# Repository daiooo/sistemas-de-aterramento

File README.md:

Sistemas de Aterramento
=======

Projeto: Sistemas de Aterramento

### Equipe:
* Ricardo Thé
* Tobias Fernandes
* Rodrigo Paulino
* Felipe Bandeira 
* Franscico Alexandre
* António Thé
* Henrique
* Rooney
* Kristian 
* Alberto de Castro

felipeband18 at gmail dot com

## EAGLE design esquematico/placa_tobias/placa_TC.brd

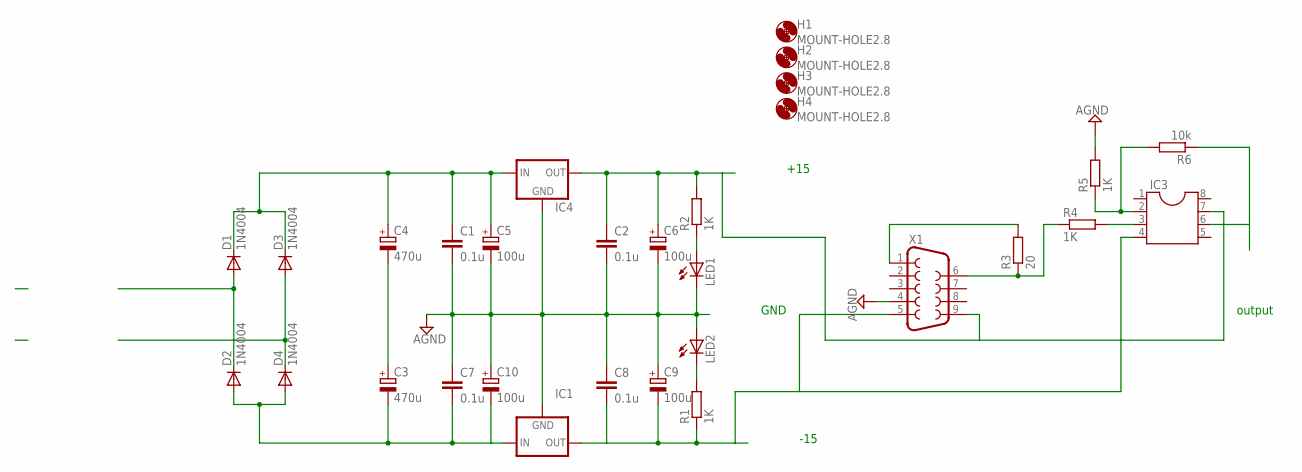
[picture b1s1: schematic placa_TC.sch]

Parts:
C1, C2, C7, C8: 0.1u; C025-024X044
C3, C4: 470u; E5-10,5
C5, C6, C9, C10: 100u; E5-10,5
D1, D2, D3, D4: 1N4004; DO41-10
H1, H2, H3, H4: MOUNT-HOLE2.8; 2,8
IC1: 79XXS
IC3: DIL8; DIL08
IC4: 78XXS
LED1, LED2: LED3MM
R1, R2, R4, R5: 1K; 0207/10
R3: 20; 0207/10
R6: 10k; 0207/10
X1: F09HP

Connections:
15V+: C1.1, C4.+, C5.+, D1.C, D3.C, IC4.IN
+15V: C2.1, C6.+, IC3.7, IC4.OUT, R2.2, X1.9
-15V: C3.-, C7.2, C10.-, D2.A, D4.A, IC1.IN
AGND: C1.2, C2.2, C5.-, C6.-, C7.1, C8.1, C9.+, C10.+, IC1.GND, IC4.GND, LED1.K (C), LED2.A, R5.2, X1.4
M15: C8.2, C9.-, IC1.OUT, IC3.4, R1.1, X1.5
unnamed: C3.+, C4.-
unnamed: D3.A, D4.C
unnamed: D1.A, D2.C
unnamed: IC3.3, R4.2
unnamed: IC3.2, R5.1, R6.2
unnamed: R3.1, R4.1, X1.6
unnamed: LED2.K (C), R1.2
unnamed: R3.2, X1.1
unnamed: LED1.A, R2.1
OUT: IC3.6, R6.1

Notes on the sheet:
output
GND
+15
-15

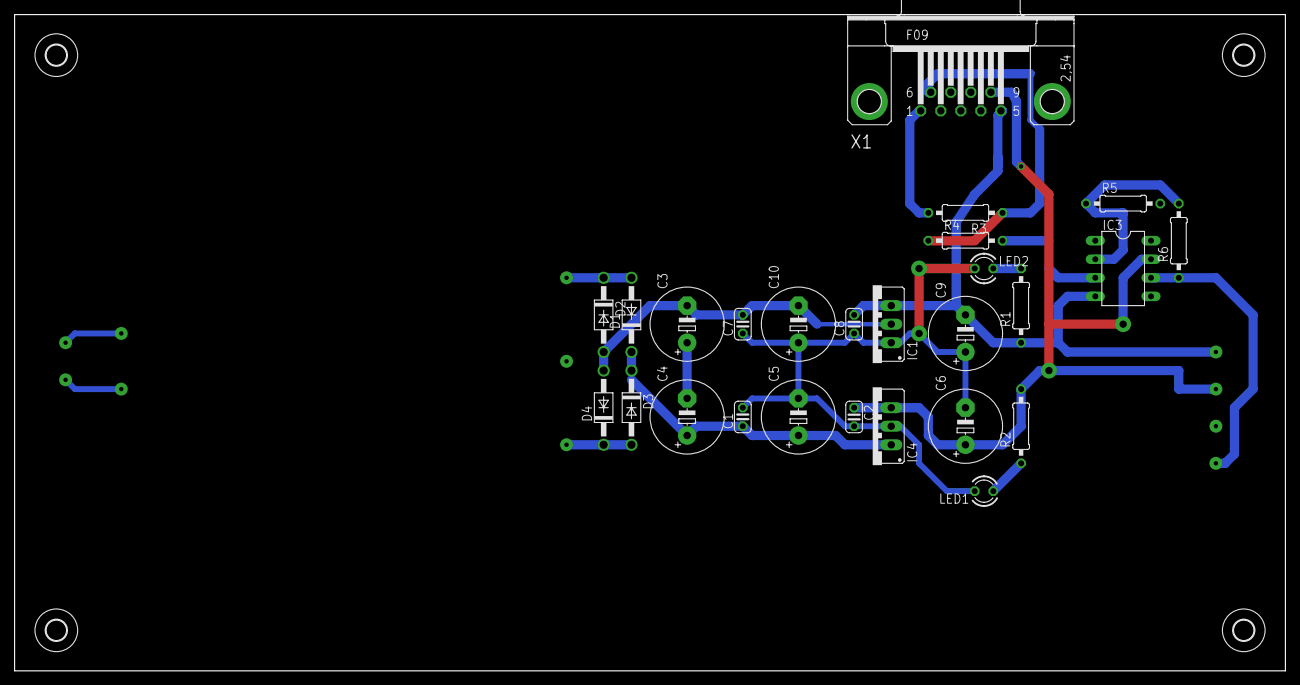
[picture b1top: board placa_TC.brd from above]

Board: 2 copper layers, 174.0 x 89.8 mm, 30 parts (0 on the bottom side), 15 nets.

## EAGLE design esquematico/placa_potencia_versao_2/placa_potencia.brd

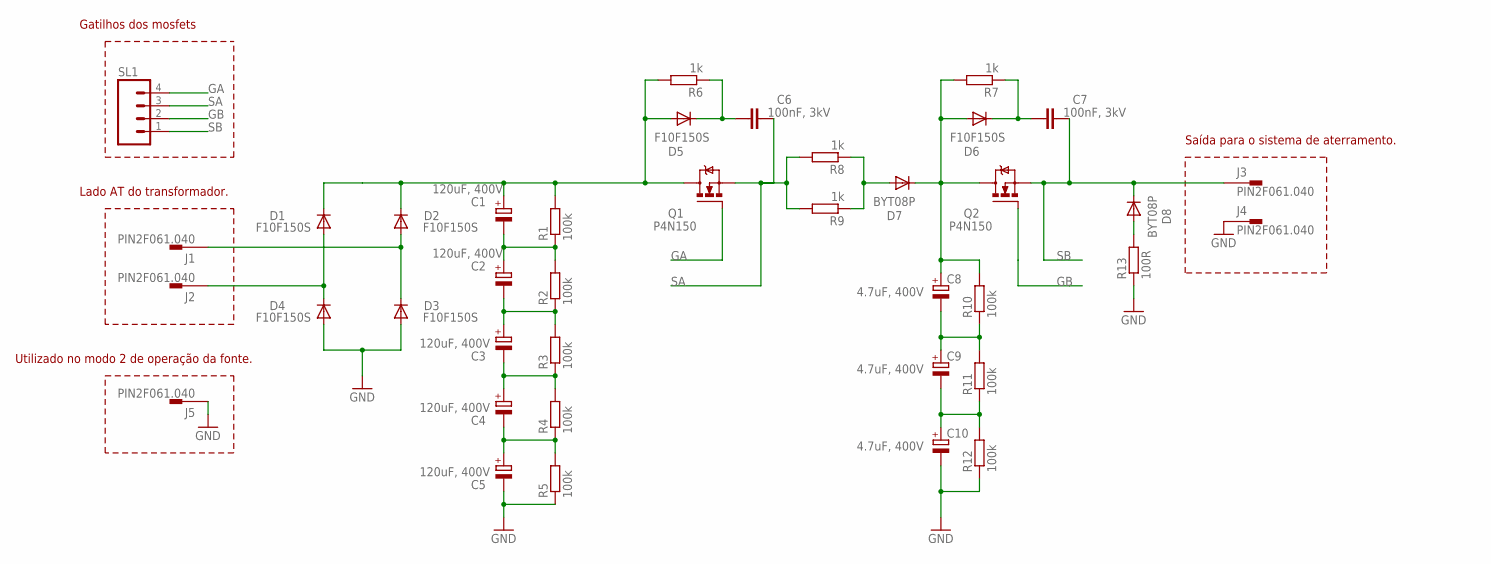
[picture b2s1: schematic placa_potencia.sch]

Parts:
C1, C2, C3, C4, C5: 120uF, 400V; E7,5-16
C6, C7: 100nF, 3kV; C050-035X075
C8, C9, C10: 4.7uF, 400V; E5-8,5
D1, D2, D3, D4, D5, D6: F10F150S; TO220ACS
D7, D8: BYT08P; TO220ACS
J1, J2, J3, J4, J5: PIN2F061.040; F061.040
Q1, Q2: P4N150; TO220BV
R1, R2, R3, R4, R5, R10, R11, R12: 100k; 0617/22
R6, R7, R8, R9: 1k; 0617/22
R13: 100R; 0617/22
SL1: M04; 04P

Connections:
GA: Q1.G, SL1.4
GB: Q2.G, SL1.2
GND: C5.-, C10.-, D3.A, D4.A, J4.A1, J4.A2, J5.A1, J5.A2, R5.1, R12.1, R13.1
unnamed: D1.A, D4.C, J2.A1, J2.A2
unnamed: D2.A, D3.C, J1.A1, J1.A2
unnamed: C1.-, C2.+, R1.1, R2.2
unnamed: C2.-, C3.+, R2.1, R3.2
unnamed: C3.-, C4.+, R3.1, R4.2
unnamed: C8.-, C9.+, R10.1, R11.2
unnamed: C6.1, D5.C, R6.1
unnamed: C4.-, C5.+, R4.1, R5.2
unnamed: D8.A, R13.2
unnamed: C7.1, D6.C, R7.1
unnamed: D7.A, R8.1, R9.1
unnamed: C1.+, D1.C, D2.C, D5.A, Q1.D, R1.2, R6.2
unnamed: C9.-, C10.+, R11.1, R12.2
SA: C6.2, Q1.S, R8.2, R9.2, SL1.3
SB: C7.2, D8.C, J3.A1, J3.A2, Q2.S, SL1.1
VCC1: C8.+, D6.A, D7.C, Q2.D, R7.2, R10.2

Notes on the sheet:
Saída para o sistema de aterramento.
Utilizado no modo 2 de operação da fonte.
Lado AT do transformador.
Gatilhos dos mosfets

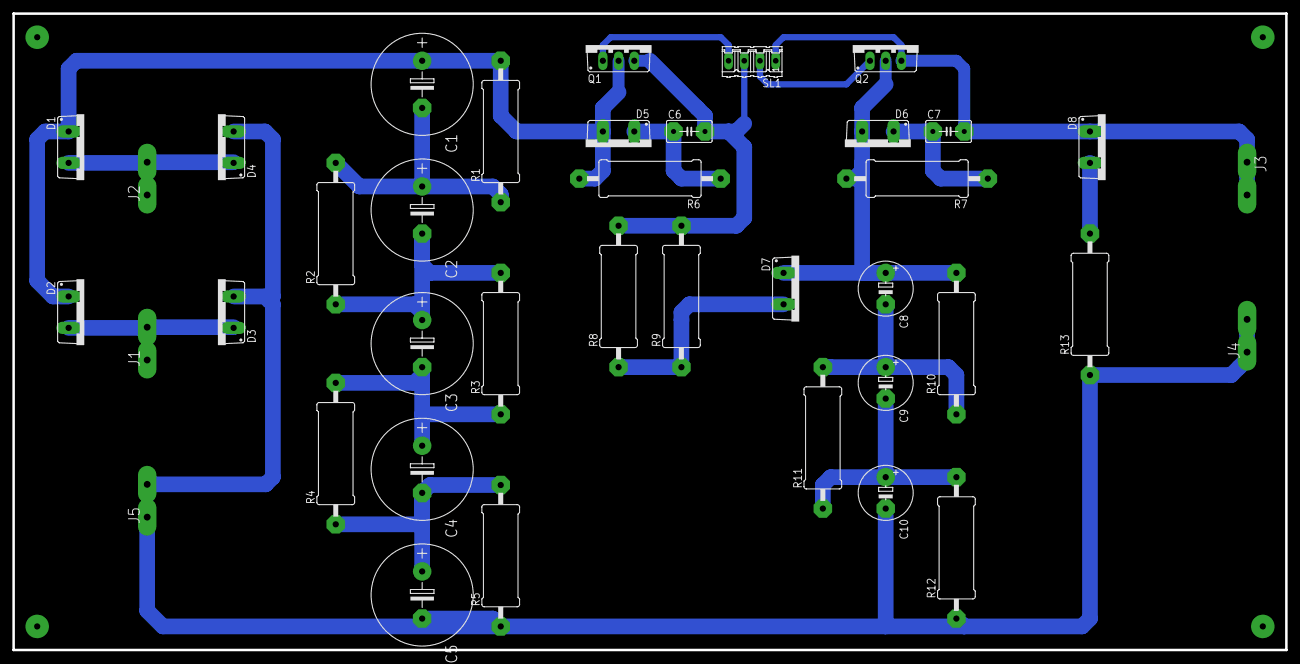
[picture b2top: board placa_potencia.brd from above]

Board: 2 copper layers, 205.7 x 102.9 mm, 39 parts (0 on the bottom side), 19 nets.

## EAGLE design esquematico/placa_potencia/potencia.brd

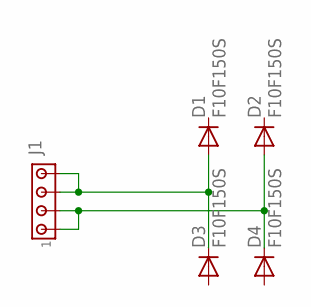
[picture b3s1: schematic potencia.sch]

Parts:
D1, D2, D3, D4: F10F150S; DO220S
J1: MTA04-156; 1X4MTA

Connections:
unnamed: D2.A, D4.C, J1.1, J1.2
unnamed: D1.A, D3.C, J1.3, J1.4

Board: 2 copper layers, 5 parts (0 on the bottom side), 2 nets, no tracks yet.

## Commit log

2015-02-09 commit inicial, repositorio antigo: https://github.com/felipeband/agilent.git
2015-02-23 fazendo as correcoes
2015-02-23 principais correções feitas, falta a correção da figura principal do software
2015-02-24 continuando o principio de funcionamento. É necessário modificar as fotos do software
2015-02-24 manual atualizado, principal e resultado
2015-02-24 Ultims detalhes
2015-02-24 figuras da apresentação e resultado alteradas. Retirado a figura da instrução do software
2015-02-24 inserção do esquematico de ligação da alimentação. encontrado pequenas referencias a fonte de forma errada
2015-02-24 atualizando o leiame
2015-02-24 testando a formatacao
2015-02-24 melhorias na figura, one -> um :)
2015-02-24 para amanhã: terminar o principio de funcionamento
2015-02-25 descrição do funcionamento, faltando ainda os classificadores
2015-02-26 correções propostas feitas, melhorias na identificação do exemplo faltando agora os classificadores na principio de funcionamento.
2015-03-03 iniciando a correção ortográfica
2015-03-03 melhor no word mesmo
2015-03-03 finalizando o processo de treinamento. inclusao de tabelas melhores. relatorio etapa 10 incluido no projeto
2015-03-04 principio de funcionamento terminado. enviar para o tobias
2015-03-04 link para o copy
2015-03-04 correções no português
2015-03-05 nao é necessário principio de funcionamento
2015-03-10 versão quyase final para o Tobias
2015-06-18 atualização dos gerbe
2015-06-18 correções nas trilhas e pads
2015-06-18 atualizando com os esquematicos iniciais
2015-06-23 atualizando o manual com a correta versao do pyvisa
2015-06-23 o pyvisa foi atualizado para versao 1.8 que é incompativel com a versao do software da fonte. Só funciona com a versao 1.4. Sem tempos para modificacoes
2015-11-26 algo no manual
2015-11-26 placa de potencia versão 2
2015-11-27 atualizando as imagens dos esquematicos
2015-12-03 placa tobias
